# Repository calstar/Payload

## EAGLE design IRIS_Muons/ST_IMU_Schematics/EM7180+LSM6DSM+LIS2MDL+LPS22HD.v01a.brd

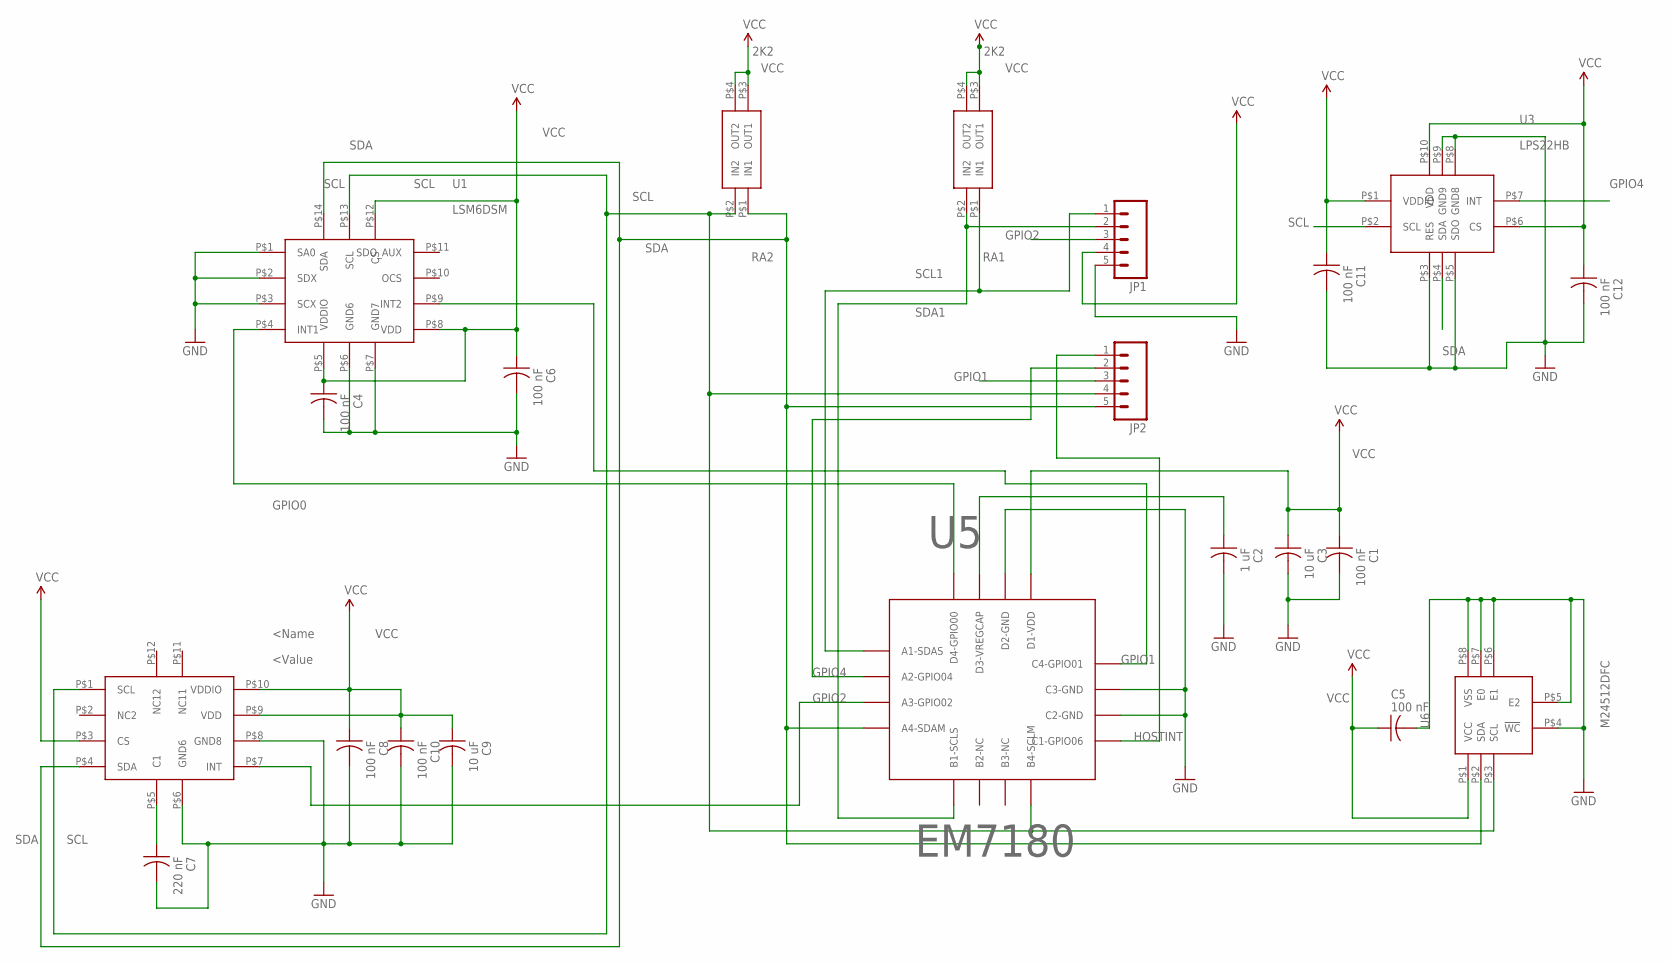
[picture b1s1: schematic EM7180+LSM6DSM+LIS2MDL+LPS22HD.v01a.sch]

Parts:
C1, C4, C5, C6, C8, C10, C11, C12: 100 nF; C0402_B
C2: 1 uF; C0402_B
C3, C9: 10 uF; C0402_B
C7: 220 nF; C0402_B
JP1, JP2: M05NO_SILK; 1X05_NO_SILK
RA1, RA2: 2K2; EXB24V
U1: LSM6DSM
U2: LIS2MDL
U3: LPS22HB
U5: EM7180; WL-CSP16
U6: M24512DFC

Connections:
GND: C1.2, C2.2, C3.2, C4.2, C5.2, C6.2, C7.2, C8.2, C9.2, C10.2, C11.2, C12.2, JP1.5, U1.P$1 (SA0), U1.P$2 (SDX), U1.P$3 (SCX), U1.P$6 (GND6), U1.P$7 (GND7), U2.P$6 (GND6), U2.P$8 (GND8), U3.P$3 (RES), U3.P$5 (SDO), U3.P$8 (GND8), U3.P$9 (GND9), U5.P$10 (C2-GND), U5.P$11 (C3-GND), U5.P$14 (D2-GND), U6.P$4 (!WC), U6.P$5 (E2), U6.P$6 (E1), U6.P$7 (E0), U6.P$8 (VSS)
GPIO0: U1.P$4 (INT1), U5.P$16 (D4-GPIO00)
GPIO1: JP2.3, U1.P$9 (INT2), U5.P$12 (C4-GPIO01)
GPIO2: JP1.3, U2.P$7 (INT), U5.P$3 (A3-GPIO02)
GPIO4: JP2.2, U3.P$7 (INT), U5.P$2 (A2-GPIO04)
HOSTINT: JP2.1, U5.P$9 (C1-GPIO06)
unnamed: C7.1, U2.P$5 (C1)
unnamed: C2.1, U5.P$15 (D3-VREGCAP)
OCS: U1.P$10 (OCS)
SCL: JP2.4, RA2.P$2 (IN2), U1.P$13 (SCL), U2.P$1 (SCL), U3.P$2 (SCL), U5.P$8 (B4-SCLM), U6.P$3 (SCL)
SCL1: JP1.1, RA1.P$1 (IN1), U5.P$1 (A1-SDAS)
SDA: JP2.5, RA2.P$1 (IN1), U1.P$14 (SDA), U2.P$4 (SDA), U3.P$4 (SDA), U5.P$4 (A4-SDAM), U6.P$2 (SDA)
SDA1: JP1.2, RA1.P$2 (IN2), U5.P$5 (B1-SCLS)
SDO_AUX: U1.P$11 (SDO_AUX)
VCC: C1.1, C3.1, C4.1, C5.1, C6.1, C8.1, C9.1, C10.1, C11.1, C12.1, JP1.4, RA1.P$3 (OUT1), RA1.P$4 (OUT2), RA2.P$3 (OUT1), RA2.P$4 (OUT2), U1.P$5 (VDDIO), U1.P$8 (VDD), U1.P$12 (CS), U2.P$3 (CS), U2.P$9 (VDD), U2.P$10 (VDDIO), U3.P$1 (VDDIO), U3.P$6 (CS), U3.P$10 (VDD), U5.P$13 (D1-VDD), U6.P$1 (VCC)

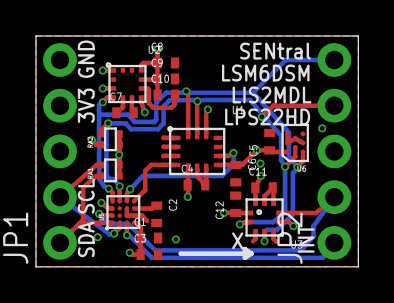
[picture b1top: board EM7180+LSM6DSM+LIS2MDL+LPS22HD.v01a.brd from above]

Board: 4 copper layers, 17.9 x 12.8 mm, 21 parts (0 on the bottom side), 13 nets.

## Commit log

2019-03-10 uploaded initial IRIS tests
2019-09-29 added humidity sensor test and IMU library+test
2019-10-29 changed SD card testing setup
2019-11-06 added joint SD card and ICM test that works
2019-11-14 Add files via upload
    I'm pretty sure the code is able to recognize start/stop commands over serial, though I don't have the correct libraries installed to test if it can record data.
2019-11-14 reorganized files to contain the tests in different sketches to avoid errors
2019-11-14 reorganizing
2019-11-15 Serial read/write: start/stop recording over serial. Should be working.
2019-11-15 shortened delays, fixed serial start/stop commands, better status messages
2019-11-20 Won't print out all data to serial monitor after stopping recording anymore.
2019-11-22 Will probably name files in the way we want them to.
2019-12-09 Create readAccelerometer
    Reads an Analog Devices ADXL3xx accelerometer and communicates the acceleration to the computer.
2019-12-09 Add files via upload
    Reads an Analog Devices ADXL3xx accelerometer and communicates the acceleration to the computer.
2020-01-31 Files are now named iteratively.
2020-02-02 Add files via upload
    Cleaned up code and removed unneeded functionality that printed all data out over serial
2020-02-07 fixed x, y, z pins labels
2020-02-12 Can read pressure and altitude now. Probably.
2020-02-15 significantly cleaned up directory structure
2020-02-15 folder re-org to make Aruduino IDE happy
2020-02-15 compiles for launch
2020-08-02 Reorganized IRIS files
2021-03-29 Started IRIS/Muons code
2021-04-04 Reworded some comments
2021-04-04 Redefined recording variables and serial commands
2021-04-11 Added IMU schematic
2021-04-18 Added basic bringup test for core
2021-04-18 moved CoreBasicTest
2021-04-18 cleaned up files strucutre to work with arduino IDE with sketchbook folder as IRIS_Muons
2021-04-18 added ADXL pins
2021-04-19 Tried to write something for ADXL and ST IMU
2021-06-02 Added Muons?
2021-06-03 Added accelerometer-only version of code under IRIS_Muons/tests
2021-06-03 added test functionality
2021-06-03 CoreBasicTest will attempt to print ST IMU data to serial monitor
2021-06-03 removed reference to vTaskDelay
2021-06-03 Fixed a single letter spelling error

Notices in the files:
parts and their libraries:
SparkFun-Connectors: Licensing: CC v3.0 Share-Alike You are welcome to use this library for commercial purposes.
SparkFun-DigitalIC: Licensing: Creative Commons ShareAlike 4.0 International - https://creativecommons.org/licenses/by-sa/4.0
